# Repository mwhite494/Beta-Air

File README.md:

# Beta Air

2016 UVM SEED Team #14: Redesigning the Pilot Interface

This repository contains the Arduino programs and other relevant files associated with the 2016 UVM SEED Team #14 engineering design project.

Photos and videos of the project:

Project Video: https://www.youtube.com/watch?v=wAZS4JNMeh0

Project Photo Album: https://www.flickr.com/gp/142660890@N02/3o64sP

RC Controller Hack Test: https://www.youtube.com/watch?v=XJeJI30qO8o

First Quadcopter Flight: https://www.youtube.com/watch?v=InLttBTRIWE

Pilot Interface Test: https://www.youtube.com/watch?v=YcpARFiyPvk

FPV Test: https://www.youtube.com/watch?v=XzfPLiM6aTw

Project Demo Flight: https://www.youtube.com/watch?v=uJsYDV2VDIQ

Project Demo GoPro Footage: https://www.youtube.com/watch?v=i7uWAD_RpNU

Flight Test GoPro Footage Part 1: https://www.youtube.com/watch?v=Y2U4ofDHF3M

Flight Test GoPro Footage Part 2 (with near crash): https://www.youtube.com/watch?v=P7VsnGtim4Y

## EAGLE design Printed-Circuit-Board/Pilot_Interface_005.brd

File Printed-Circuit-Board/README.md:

These are the board files for the attempt at a custom PCB shield designed in Eagle that would neatly package the pilot interface circuitry.
Unfortunately the board did not work consistently enough to use with the prototype but a future SEED team may wish to
look at these if they choose to make edits to the board for future iterations of the project.
This board uses some custom packages located in MTW.lbr.

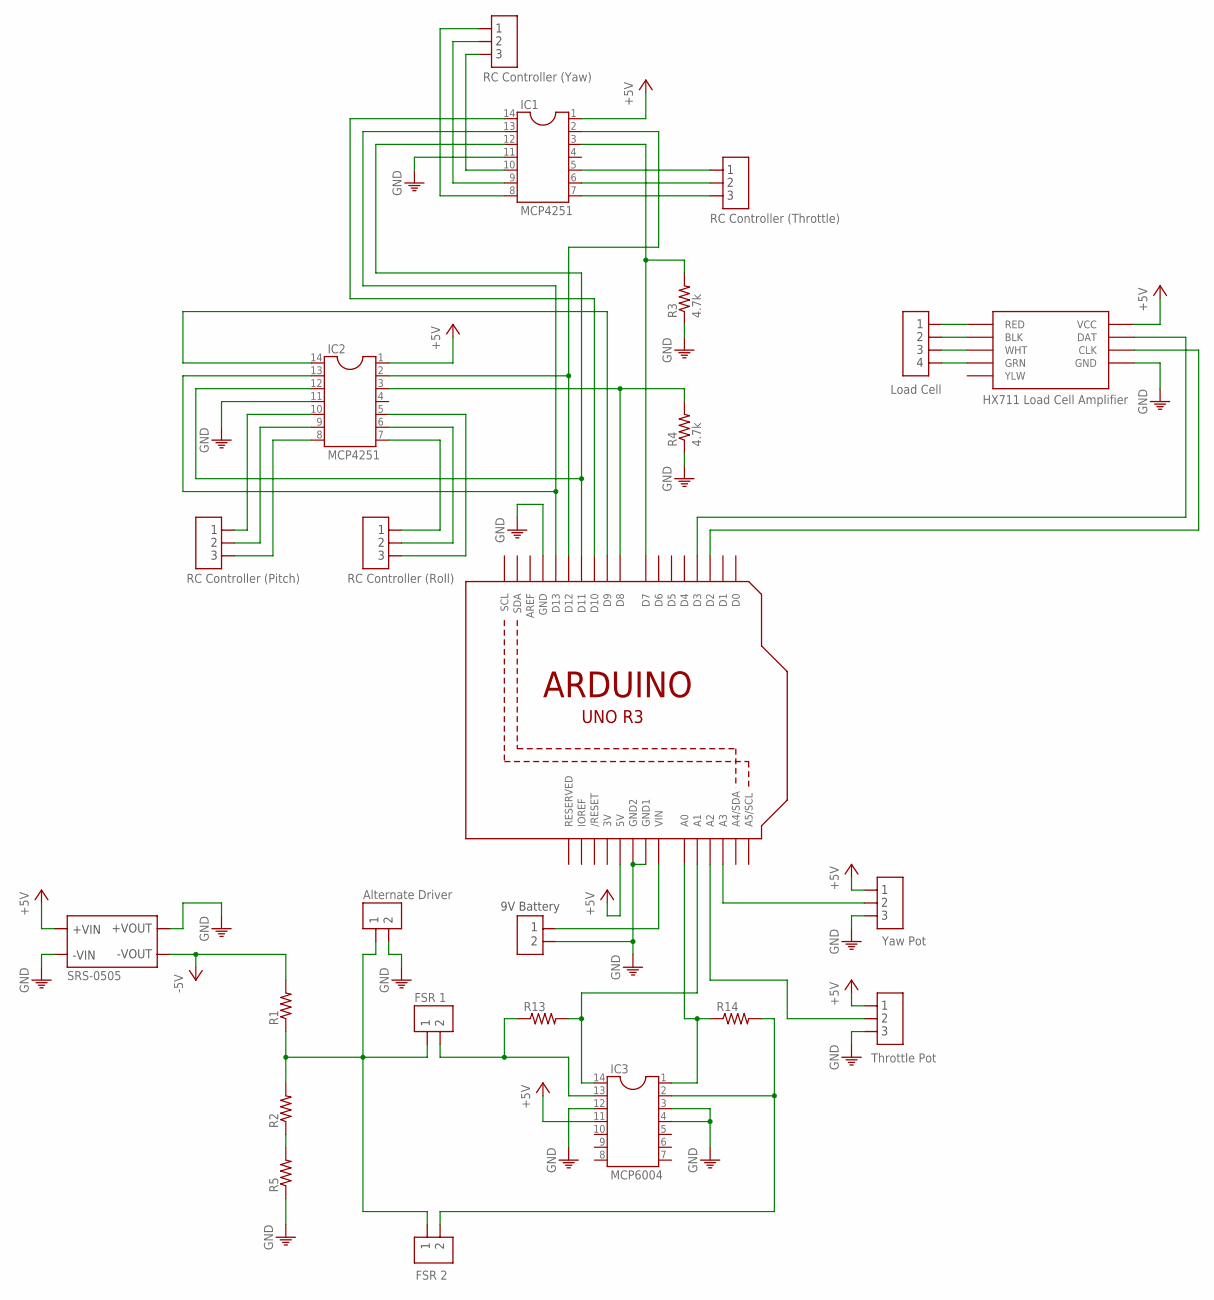
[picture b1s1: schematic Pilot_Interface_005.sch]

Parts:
IC1, IC2: MCP4251; DIL14
IC3: MCP6004; DIL14
R1, R2, R5, R13, R14: R-US_0204/2V; 0204V
R3, R4: 4.7k; 0204V
U1: ARDUINOR3
U$1: HX711
U$2, U$3, U$6, U$7, U$10, U$11: PAD_3
U$4, U$5, U$12, U$13: PAD_2
U$8: PAD_4
U$9: SRS-0505

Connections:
3V: U1.3V
+5V: IC1.1 (14), IC2.1 (14), IC3.11 (4), U1.5V, U$1.VCC, U$6.P$1, U$7.P$1, U$9.P$1 (+VIN), U$9.P$16 (+VIN)
-5V: R1.2, U$9.P$6 (-VOUT), U$9.P$11 (-VOUT)
unnamed: U$1.RED, U$8.P$1
unnamed: U$1.BLK, U$8.P$2
unnamed: U$1.WHT, U$8.P$3
unnamed: U$1.GRN, U$8.P$4
unnamed: IC3.2 (13), R14.2, U$5.P$2
unnamed: U1.D2, U$1.CLK
unnamed: U1.D3, U$1.DAT
unnamed: IC3.14 (1), R13.2, U1.A1
unnamed: IC3.1 (14), R14.1, U1.A0
unnamed: U1.A3, U$6.P$2
unnamed: U1.A2, U$7.P$2
unnamed: R1.1, R2.2, U$4.P$1, U$5.P$1, U$12.P$1
unnamed: IC2.14 (1), U1.D9
unnamed: IC1.14 (1), U1.D10
unnamed: IC1.13 (2), IC2.13 (2), U1.D13
unnamed: IC1.12 (3), IC2.12 (3), U1.D11
unnamed: IC1.2 (13), IC2.2 (13), U1.D12
unnamed: IC1.3 (12), R3.2, U1.D7
unnamed: IC2.3 (12), R4.2, U1.D8
unnamed: IC1.5 (10), U$3.P$1
unnamed: IC1.6 (9), U$3.P$2
unnamed: IC1.7 (8), U$3.P$3
unnamed: IC1.10 (5), U$2.P$3
unnamed: IC1.9 (6), U$2.P$2
unnamed: IC1.8 (7), U$2.P$1
unnamed: IC2.8 (7), U$10.P$3
unnamed: IC2.9 (6), U$10.P$2
unnamed: IC2.10 (5), U$10.P$1
unnamed: IC2.7 (8), U$11.P$1
unnamed: IC2.6 (9), U$11.P$2
unnamed: IC2.5 (10), U$11.P$3
unnamed: IC3.13 (2), R13.1, U$4.P$2
unnamed: R2.1, R5.2
unnamed: U1.VIN, U$13.P$1
PE: IC1.11 (4), IC2.11 (4), IC3.3 (12), IC3.4 (11), IC3.12 (3), R3.1, R4.1, R5.1, U1.GND, U1.GND1, U1.GND2, U$1.GND, U$6.P$3, U$7.P$3, U$9.P$7 (+VOUT), U$9.P$8 (-VIN), U$9.P$9 (-VIN), U$9.P$10 (+VOUT), U$12.P$2, U$13.P$2

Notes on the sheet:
FSR 1
FSR 2
Throttle Pot
Yaw Pot
Load Cell
RC Controller (Yaw)
RC Controller (Throttle)
RC Controller (Pitch)
RC Controller (Roll)
Alternate Driver
9V Battery

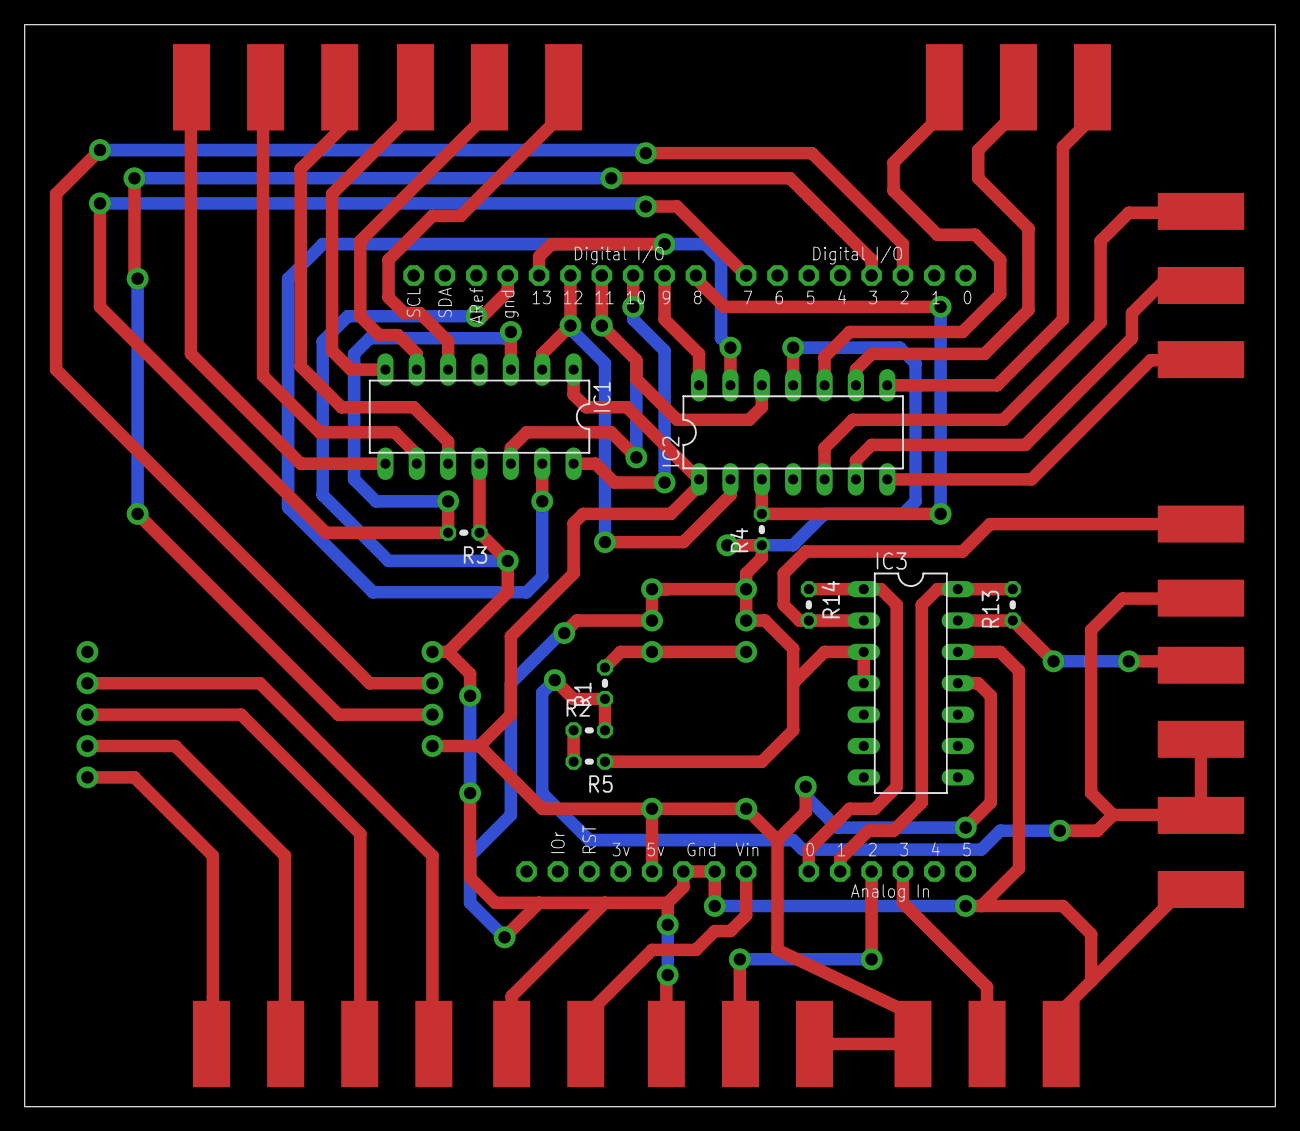
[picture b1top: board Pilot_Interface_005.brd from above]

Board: 2 copper layers, 101.3 x 87.6 mm, 24 parts (0 on the bottom side), 37 nets.

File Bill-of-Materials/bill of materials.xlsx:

Item | Description |  | Cost
Motorcycle platform
Iron thread fitting round head cap | Cap and collar for central support | 1.0 | 43.81 | McMaster-Carr
3.906" OD .393" wire diameter spring | Springs for central support | 2.0 | 52.26 | McMaster-Carr
Steel-wall pipe 4" OD, threaded on one end | Central support | 36" | 134.64 | McMaster-Carr
Subaru Outback Driveshaft | U-joint for central support | 1.0 | 75.0 | Rathe's Salvage Yard
1988 Suzuki Katana Frame | Rolling motorcycle chassis | 1.0 | 300.0 | Craigslist
1 in by 1 in Cube Steel | Material for motorcycle stand | 9 ft | 36.0 | Aubuchon Hardware
1/4" thick stainless steel plate | Material for motion platform and frame modification | 4x18" | 75.0 | McMaster-Carr
3/8" thick stainless steel plate | material for motor arms | 4x6" | 31.64 | McMaster-Carr
3/4x16" hex nuts | interface between Heim joints and Motors | 10.0 | 12.0 | McMaster-Carr
3/4" steel rod | U-joint for central support | 1.0 | 75.0 | Rathe's Salvage Yard
10 kohm analog potentiometers | Potentiometers for throttle assembly | 1.0 | 0.95 | Sparkfun
75 kohm precision potentiometers | Potentiometer for measuring handlebar rotation | 1.0 | 10.0 | Marco
3D Printed ABS Plastic | Custom parts for potentiometer assemblies | ~5 cubic in | 5.0 | UVM FabLab
9V Batteries | Batteries for Arduinos | 2.0 | 10.0 | Marco
Breadboard | For testing pilot interface circuit | 1.0 | 1.0 | Marco
Arduino Uno | Microcontroller platform | 3.0 | 20.0 | Marco, Jake, Casey
Force Sensitive Resistors (FSR) | Pressure sensors at rider's knees | 2.0 | 15.9 | Sparkfun
MCP6004 | Op-amps for FSRs | 1.0 | 0.48 | Mouser
SRS-0505 | 5V-5V DC-DC converter to drive FSRs | 1.0 | 7.34 | Mouser
10 kg Load Cell (TAL201) | For measuring pitch input on the handlebars | 1.0 | 11.95 | Sparkfun
HX711 Load Cell Amplifier | Amplifier board for the load cell | 1.0 | 9.95 | Sparkfun
MCP4251 | 10 kohm digital potentiometers | 2.0 | 2.04 | Mouser
4.7 kohm Resistors |  | 2.0 | 0.1 | Marco
750 ohm Resistors |  | 2.0 | 0.05 | Marco
680 ohm Resistors |  | 1.0 | 0.05 | Marco
33 ohm Resistors |  | 2.0 | 0.05 | Marco
14.8V Lipo Batteries | Batteries for the quadcopter | 2.0 | 66.45 | Friend of Jake
7.4V Lipo Battery | Battery for the FPV transmitter | 1.0 | 25.0 | Jake
Lipo Battery Charger |  | 1.0 | 20.0 | Jake
Lipo Safe Charging Bag |  | 1.0 | 3.0 | Jake
FPV Transmitter / Reciever |  | 1.0 | 75.0 | Helipal
12 V Power Supply | Power supply for FPV reciever | 1.0 | 15.0 | Kyle
GoPro Hero 3+ | FPV Camera | 1.0 | 300.0 | Marco
Modified GoPro Case |  | 1.0 | - | Marco
RCA Adapter Plug | To connect RC reciever to TV | 1.0 | 4.0 | Helipal
TV |  | 1.0 | 200.0 | Austin
NAZA Lite Flight Controller | Flight controller for the quadcopter | 1.0 | 180.0 | Helipal
Spektrum RC Reciever | Reciever connected to the flight controller | 1.0 | 15.0 | Jake
Spektrum DX6i Controller | Master and slave controllers | 2.0 | 260.0 | Jake
Trainer cable | Cable to connected master and slave controllers | 1.0 | 8.0 | Jake
 |  | Total: | $2,094
